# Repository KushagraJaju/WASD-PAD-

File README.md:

# WASD-PAD

A small 4‑key macropad based on the Seeed XIAO RP2040, customized to act as WASD keys for gaming and shortcuts.  
The board uses MX‑style switches, SK6812‑MINI addressable RGB LEDs, and a 3D‑printed case inspired by the Hack Club Hackpad project.

---

## Features

- 4 mechanical MX‑style switches laid out as WASD
- Seeed XIAO RP2040 as the main controller
- KMK firmware running on CircuitPython
- 4 SK6812‑MINI RGB LEDs for per‑key lighting
- Custom PCB designed in KiCad
- 3D‑printed top and bottom case

---

## Hardware

- 1 × Seeed XIAO RP2040 module  
- 4 × MX‑style mechanical switches  
- 4 × SK6812‑MINI addressable RGB LEDs  
- Custom PCB (KiCad files in `Hardware/`)

- 3D‑printed case (Fusion 360 / STEP files in `Case/`)

See `BOM.xlsv` for the full bill of materials.

---

## Firmware

The firmware is written with KMK:

- Source in the `Firmware/` folder (main file: `firmware.main.py`)
- Keys are wired to XIAO pins D0–D3 and mapped to `W`, `A`, `S`, `D`
- Plug the board in, copy `firmware.main.py` to the CIRCUITPY drive, and it will enumerate as a USB keyboard

---

## Getting Started

1. **Assemble the PCB**  
   - Solder the XIAO RP2040, switches, LEDs, and passives.  
2. **Flash CircuitPython & KMK**  
   - Install CircuitPython on the XIAO and copy the KMK library folder.  
3. **Copy firmware**  
   - Copy `Firmware/firmware.main.py` to the CIRCUITPY drive.  
4. **Print and assemble case**  
   - 3D print the case parts and assemble with M3 screws and heat‑set inserts.

---

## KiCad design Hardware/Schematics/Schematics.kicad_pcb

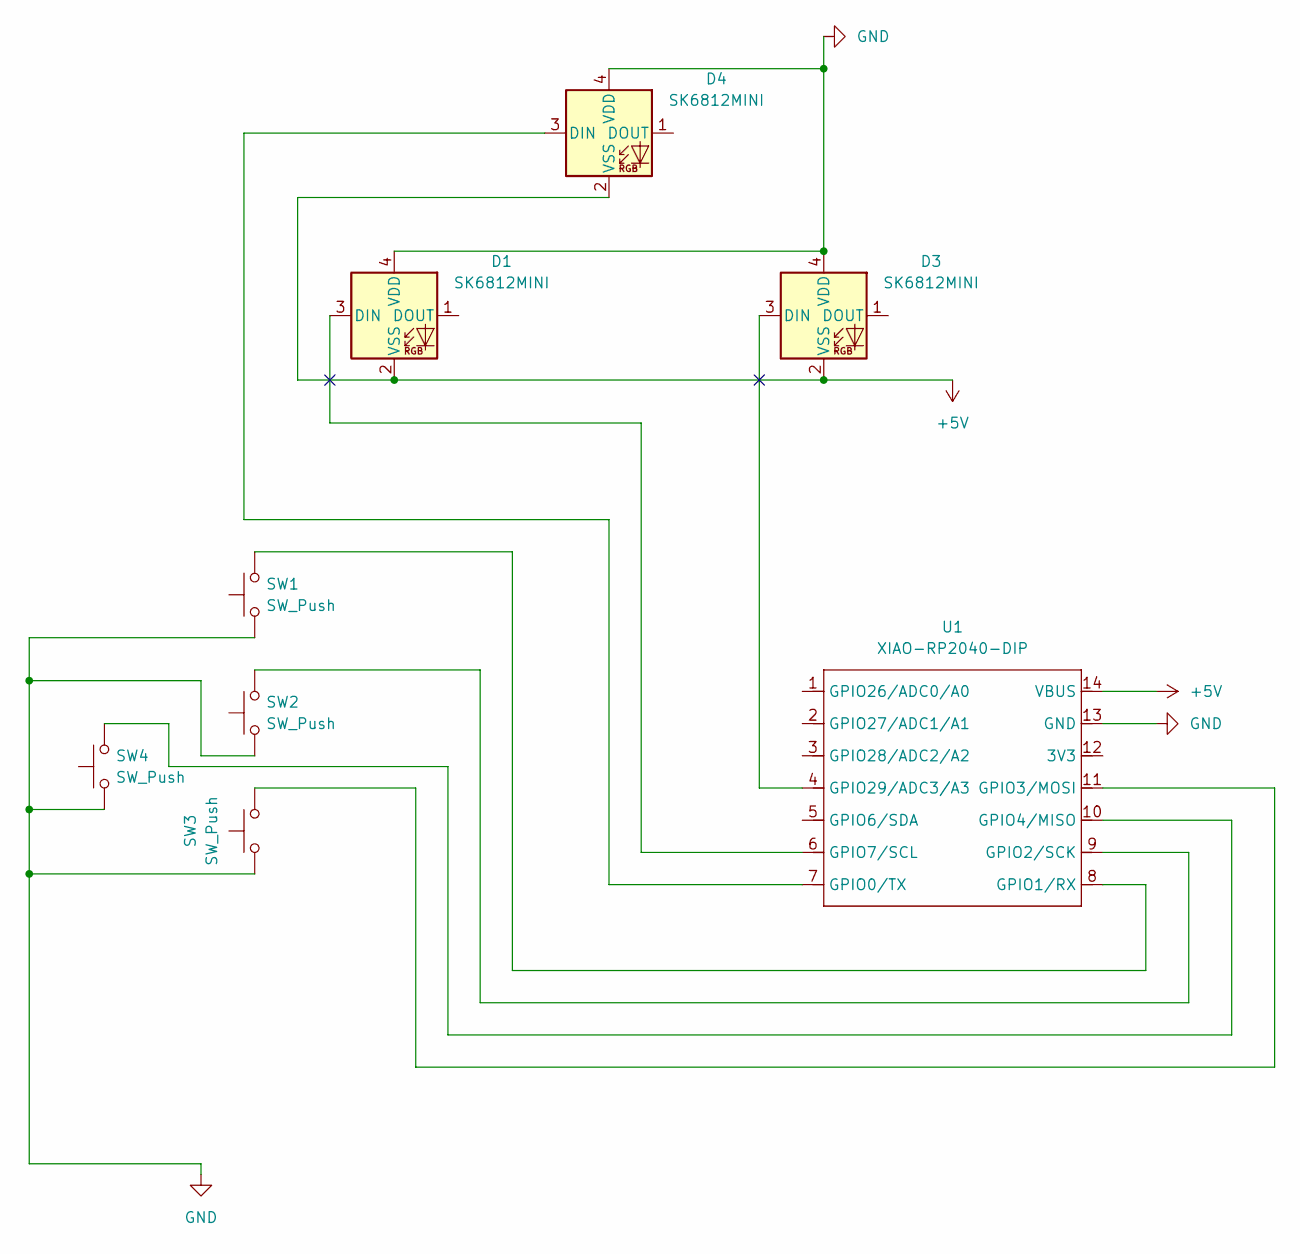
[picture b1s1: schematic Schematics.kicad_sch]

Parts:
D1, D3, D4: SK6812MINI; LED_SK6812MINI_PLCC4_3.5x3.5mm_P1.75mm
SW1, SW2, SW3, SW4: SW_Push; SW_Cherry_MX_1.00u_PCB
U1: XIAO-RP2040-DIP

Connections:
+5V: D1.2 (VSS), D3.2 (VSS), D4.2 (VSS), U1.14 (VBUS)
GND: D1.4 (VDD), D3.4 (VDD), D4.4 (VDD), SW1.1, SW2.1, SW3.1, SW4.1, U1.13 (GND)
unnamed: D1.3 (DIN), U1.6 (GPIO7/SCL)
unnamed: D3.3 (DIN), U1.4 (GPIO29/ADC3/A3)
unnamed: D4.3 (DIN), U1.7 (GPIO0/TX)
unnamed: SW1.2, U1.8 (GPIO1/RX)
unnamed: SW2.2, U1.9 (GPIO2/SCK)
unnamed: SW3.2, U1.11 (GPIO3/MOSI)
unnamed: SW4.2, U1.10 (GPIO4/MISO)

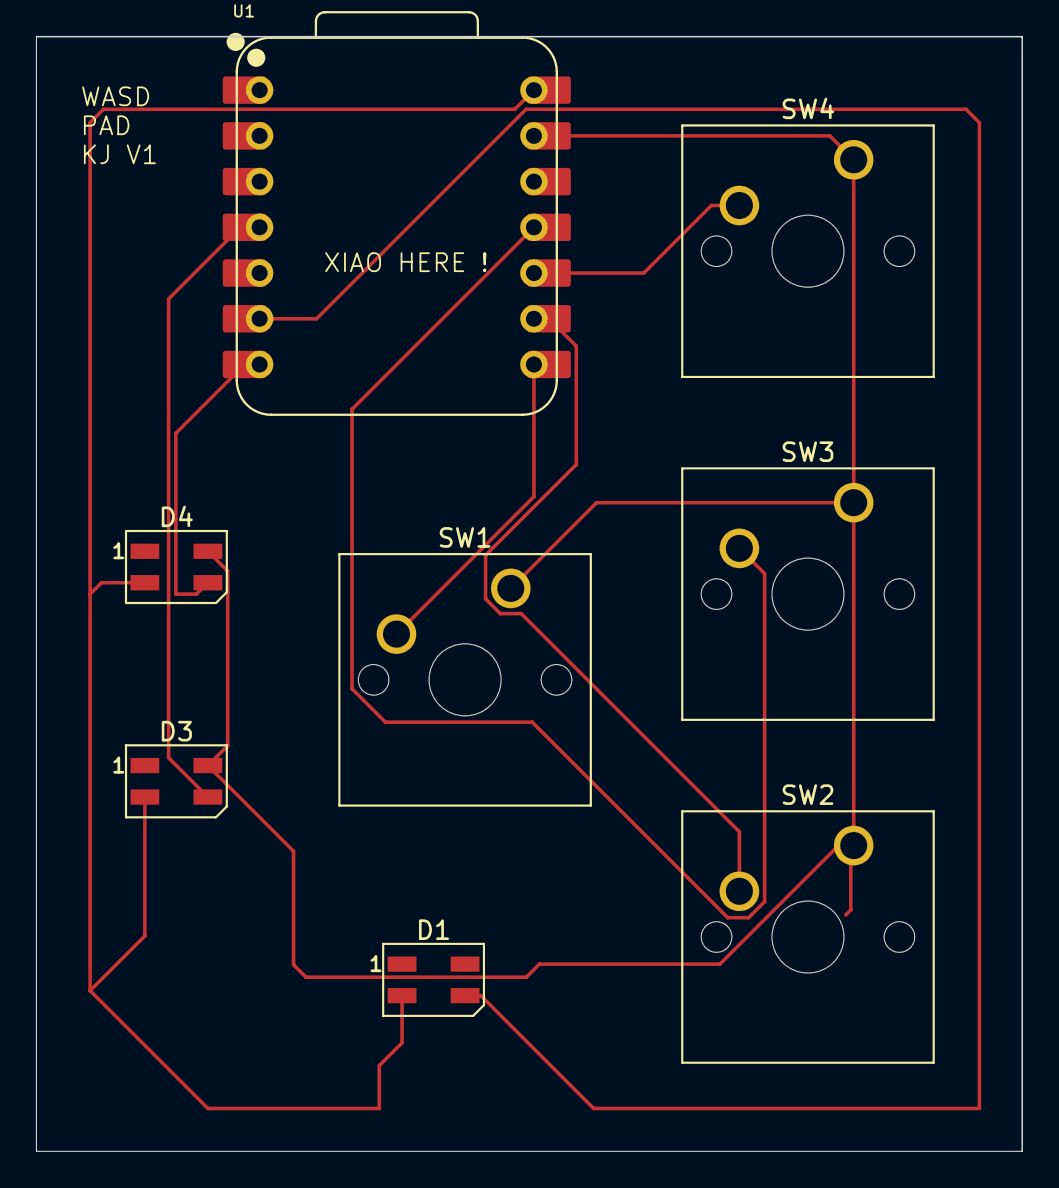
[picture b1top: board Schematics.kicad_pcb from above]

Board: 2 copper layers, 54.8 x 61.9 mm, 8 parts (0 on the bottom side), 9 nets.

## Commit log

2025-12-03 Added all the files
2025-12-03 Added Schematic image with PCB version
    Updated schematic image reference in README.
